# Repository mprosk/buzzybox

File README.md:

# buzzybox
Simple multi oscillator drone box

## Design and Assembly Notes
- More or less any NPN transistor will work, but not all transistors will go into reverse avalanche mode. I recommend you test one of the transistors you intend to use on a breadboard to make sure they will oscillate. Refer to the circuit in the reverse avalanche article in the `datasheets` folder
- The base lead of the transistors needs to be snipped, otherwise the oscillator may not work. Refer to the reverse avalanche article in the `datasheets` folder
- The footprint for the potentiometers is a little off and you may need to widen the mounting holes with a drill (the electrical holes are fine)
- The footprint for the headphone jack is upside down so it needs to go on the underside of the bottom board, not on top
- The output level is stupid low so just be aware it's going to require a lot of amplification to be useful
- Voltage range can be anything from 12-24 ish volts. Increasing the supply voltage will increase the relative pitch of all oscillators

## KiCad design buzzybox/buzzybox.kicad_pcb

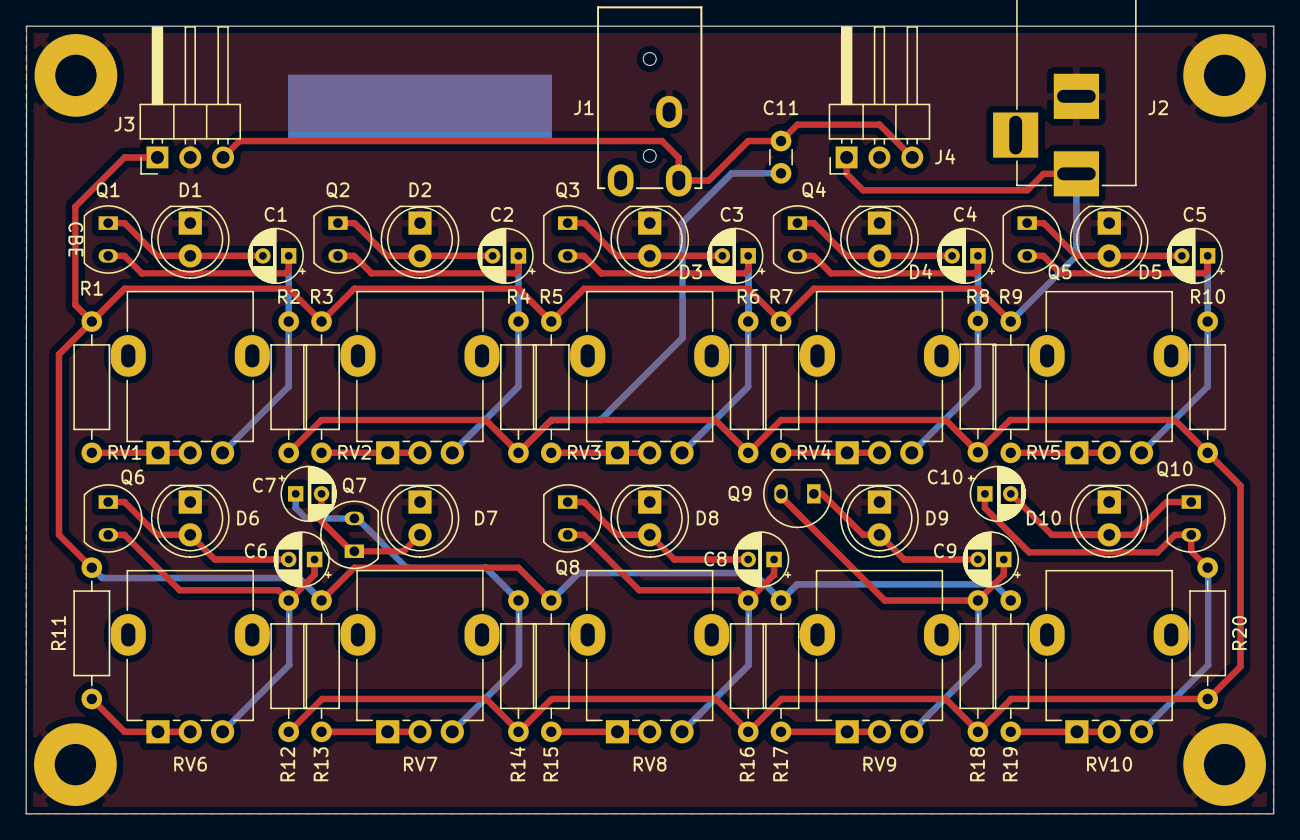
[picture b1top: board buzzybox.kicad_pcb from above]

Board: 2 copper layers, 96.6 x 61.0 mm, 69 parts (0 on the bottom side), 34 nets.

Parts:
C1, C2, C3, C4, C5, C6, C7, C8, C9, C10: CP1; CP_Radial_D4.0mm_P2.00mm
C11: 0.1uF; C_Disc_D3.0mm_W1.6mm_P2.50mm
D1, D2, D3, D4, D5, D6, D7, D8, D9, D10: LED; LED_D5.0mm
H1, H2, H3, H4: M3; MountingHole_3.2mm_M3_Pad
J1: AudioJack3; STX-3000
J2: Barrel_Jack; BARREL_JACK
J3, J4: Conn_01x03; PinHeader_1x03_P2.54mm_Horizontal
Q1, Q2, Q3, Q4, Q5, Q6, Q7, Q8, Q9, Q10: Q_NPN_CBE; TO-92-2
R1, R3, R5, R7, R9, R11, R13, R15, R17, R19: 1k; R_Axial_DIN0207_L6.3mm_D2.5mm_P10.16mm_Horizontal
R2, R4, R6, R8, R10, R12, R14, R16, R18, R20: 100k; R_Axial_DIN0207_L6.3mm_D2.5mm_P10.16mm_Horizontal
RV1, RV2, RV3, RV4, RV5, RV6, RV7, RV8, RV9, RV10: 10k; Potentiometer_Alpha_RD901F-40-00D_Single_Vertical

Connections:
+VDC: J2.1, J3.1, J4.1, R1.1, R3.1, R5.1, R7.1, R9.1, R11.1, R13.1, R15.1, R17.1, R19.1
/oscillator/OSC_OUT: C11.1, R2.1, R4.1, R6.1, R8.1, R10.1, R12.1, R14.1, R16.1, R18.1, R20.1
GND: D1.1, D2.1, D3.1, D4.1, D5.1, D6.1, D7.1, D8.1, D9.1, D10.1, H1.1, H2.1, H3.1, H4.1, J1.S, J2.2, J3.2, J4.2
unnamed: C1.1, Q1.3, R2.2, RV1.3
unnamed: C1.2, D1.2, Q1.1
unnamed: C2.1, Q2.3, R4.2, RV2.3
unnamed: C2.2, D2.2, Q2.1
unnamed: C3.1, Q3.3, R6.2, RV3.3
unnamed: C3.2, D3.2, Q3.1
unnamed: C4.1, Q4.3, R8.2, RV4.3
unnamed: C4.2, D4.2, Q4.1
unnamed: C5.1, Q5.3, R10.2, RV5.3
unnamed: C5.2, D5.2, Q5.1
unnamed: C6.1, Q6.3, R12.2, RV6.3
unnamed: C6.2, D6.2, Q6.1
unnamed: C7.1, Q7.3, R14.2, RV7.3
unnamed: C7.2, D7.2, Q7.1
unnamed: C8.1, Q8.3, R16.2, RV8.3
unnamed: C8.2, D8.2, Q8.1
unnamed: C9.1, Q9.3, R18.2, RV9.3
unnamed: C9.2, D9.2, Q9.1
unnamed: C10.1, Q10.3, R20.2, RV10.3
unnamed: C10.2, D10.2, Q10.1
unnamed: C11.2, J1.T, J3.3, J4.3
unnamed: R1.2, RV1.1, RV1.2
unnamed: R3.2, RV2.1, RV2.2
unnamed: R5.2, RV3.1, RV3.2
unnamed: R7.2, RV4.1, RV4.2
unnamed: R9.2, RV5.1, RV5.2
unnamed: R11.2, RV6.1, RV6.2
unnamed: R13.2, RV7.1, RV7.2
unnamed: R15.2, RV8.1, RV8.2
unnamed: R17.2, RV9.1, RV9.2
unnamed: R19.2, RV10.1, RV10.2

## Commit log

2020-12-15 Initial layout complete
2020-12-15 complete mini layout
2020-12-17 Add faceplate
2020-12-17 finalize main PCB after parts recieved
2020-12-18 complete refit
2022-04-10 Add gerber files
2022-04-10 Update to KiCAD6 and created schematic PDF
2022-04-10 Include PDF of schematic
